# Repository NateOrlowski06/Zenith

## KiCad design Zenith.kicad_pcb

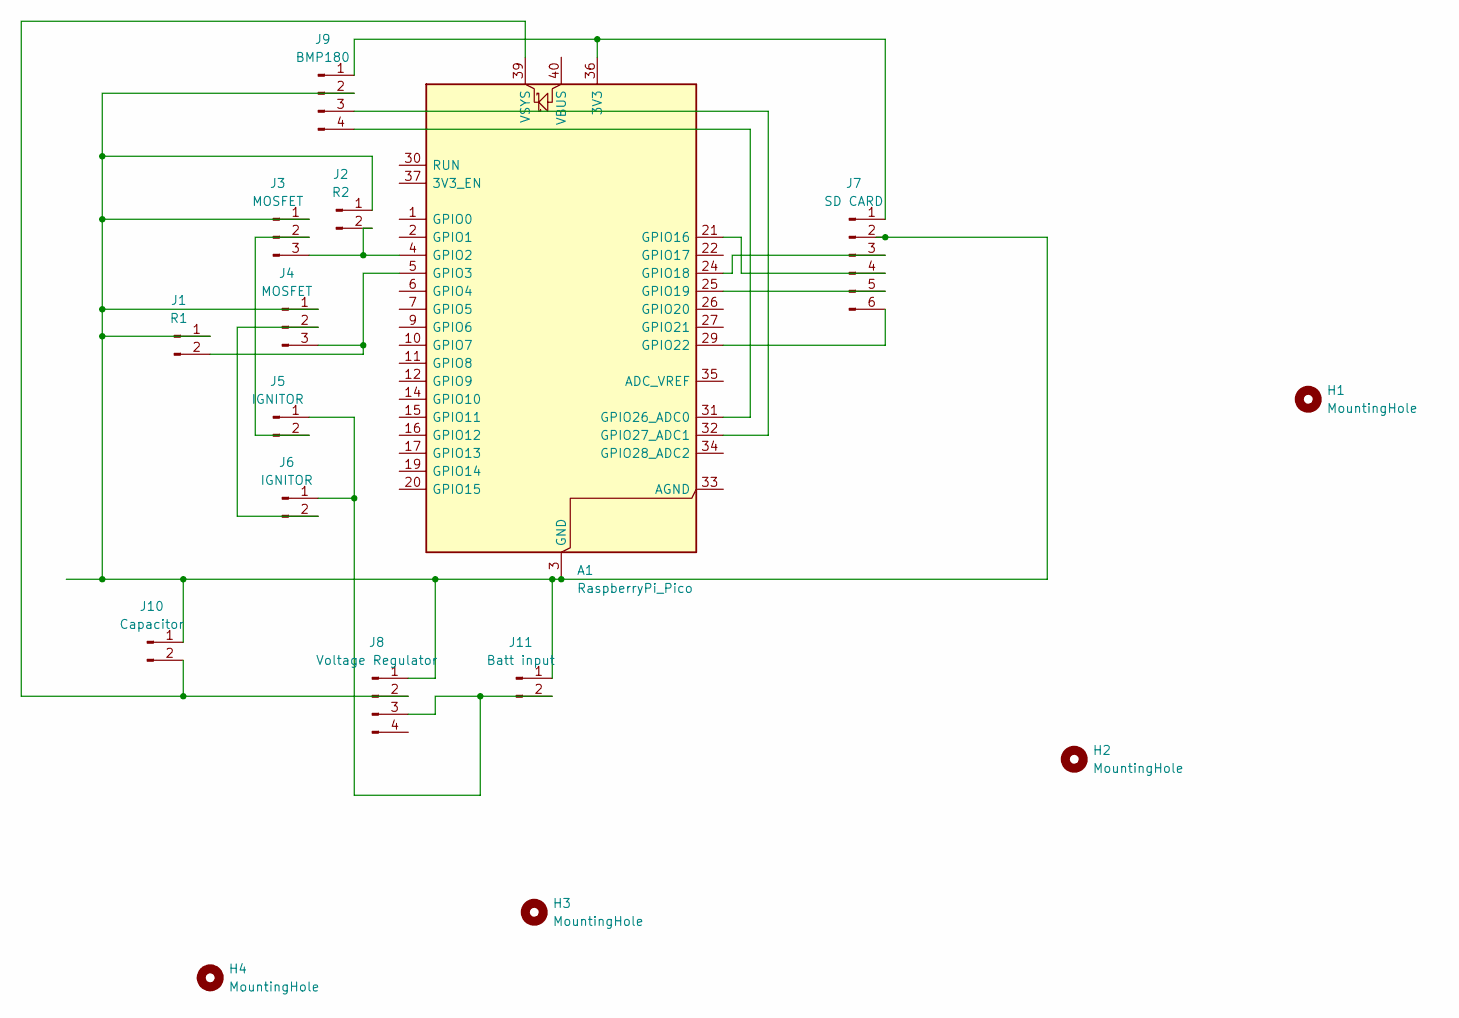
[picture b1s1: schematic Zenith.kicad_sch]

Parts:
A1: RaspberryPi_Pico; RaspberryPi_Pico_Common_Unspecified
H1, H2, H3, H4: MountingHole; MountingHole_2.2mm_M2
J1: R1; PinSocket_1x02_P2.54mm_Vertical
J2: R2; PinSocket_1x02_P2.54mm_Vertical
J3, J4: MOSFET; PinSocket_1x03_P2.54mm_Vertical
J5, J6: IGNITOR; PinSocket_1x02_P2.54mm_Vertical
J7: SD CARD; PinSocket_1x06_P2.54mm_Vertical
J8: Voltage Regulator; PinSocket_1x04_P2.54mm_Vertical
J9: BMP180; PinSocket_1x04_P2.54mm_Vertical
J10: Capacitor; PinSocket_1x02_P2.54mm_Vertical
J11: Batt input; PinSocket_1x02_P2.54mm_Vertical

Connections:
unnamed: A1.36 (3V3), J7.1, J9.1
unnamed: A1.4 (GPIO2), J2.2, J3.3
unnamed: A1.5 (GPIO3), J1.2, J4.3
unnamed: A1.21 (GPIO16), J7.4
unnamed: A1.24 (GPIO18), J7.3
unnamed: A1.25 (GPIO19), J7.5
unnamed: A1.29 (GPIO22), J7.6
unnamed: A1.31 (GPIO26_ADC0), J9.4
unnamed: A1.32 (GPIO27_ADC1), J9.3
unnamed: A1.39 (VSYS), J8.2, J10.2
unnamed: A1.3 (GND), A1.8 (GND), A1.13 (GND), A1.18 (GND), A1.23 (GND), A1.28 (GND), A1.38 (GND), J1.1, J2.1, J3.1, J4.1, J7.2, J8.1, J9.2, J10.1, J11.1
unnamed: J3.2, J5.2
unnamed: J4.2, J6.2
unnamed: J5.1, J6.1, J8.3, J11.2

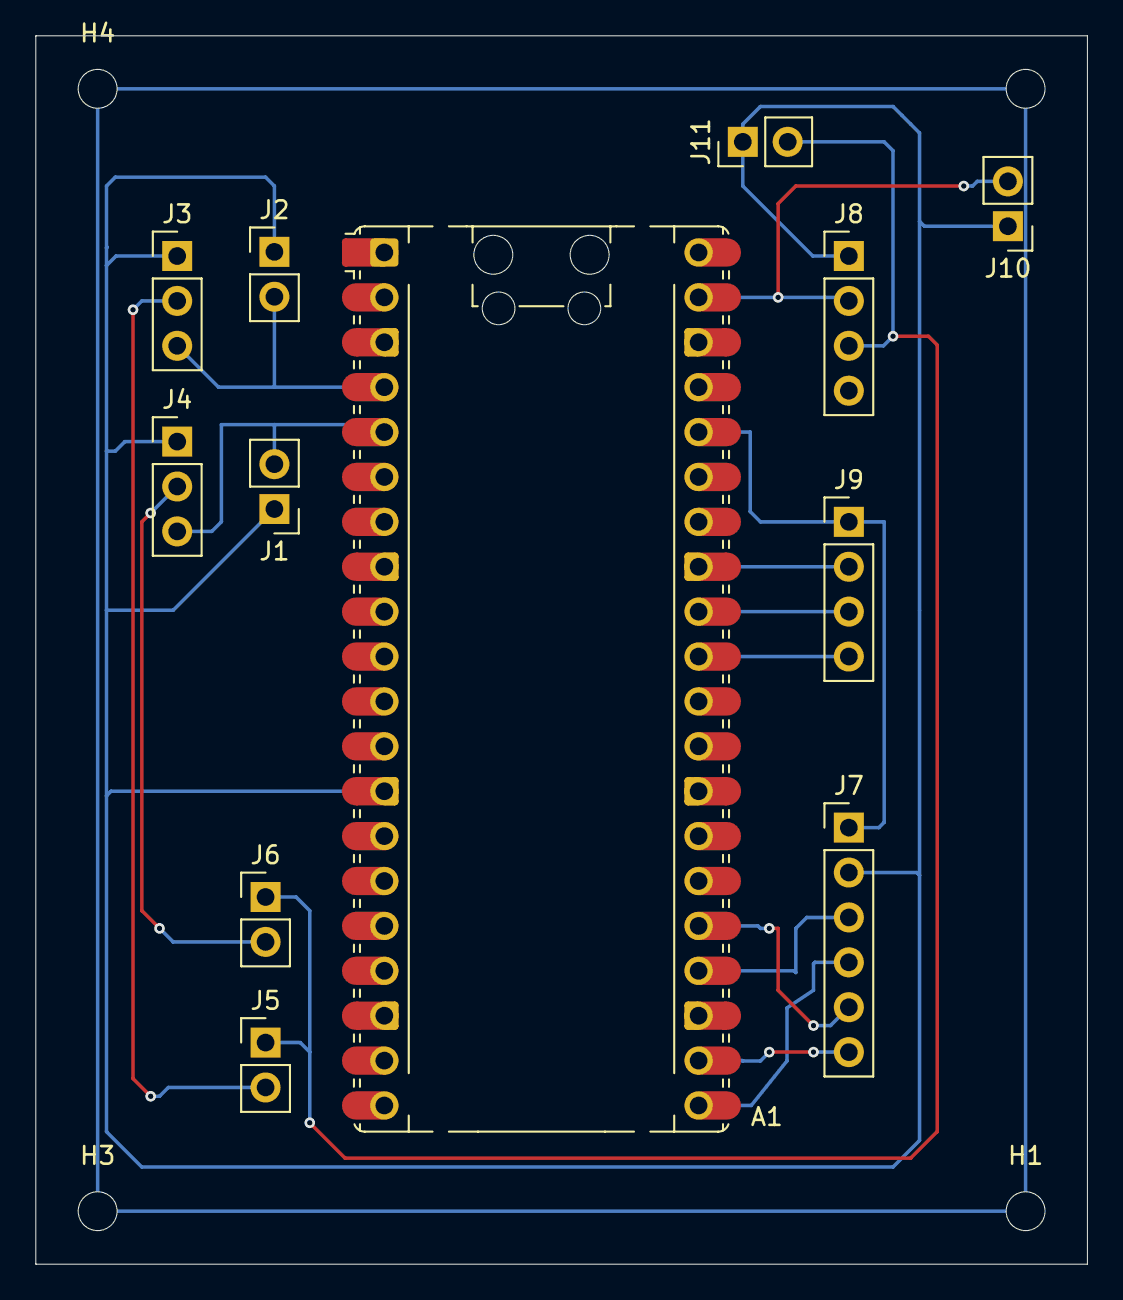
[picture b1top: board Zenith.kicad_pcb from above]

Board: 2 copper layers, 59.5 x 69.5 mm, 16 parts (0 on the bottom side), 14 nets.

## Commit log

2025-05-15 Added BMP180 library
2025-05-15 Added altitude calculation, added scripts to .gitignore
2025-05-15 Pressure Sensor testing
2025-05-16 Changed bmp180 from header only file. Implemented struct data structure for altimeter values. Tested altimeter readings. Wrote some skeleton code for altimeter funcitons.
2025-05-16 Fixed path errors, due to changing file location of bmp180 libraries
2025-05-16 Circular linked list addition
2025-05-16 Impletmented moving average utilizing circular linked list.
2025-05-16 Comments
2025-05-16 Conversion to us instead of ms for more accurate sleep calls
2025-05-16 Slight library optimizations
2025-05-16 Implemented velocity calculations and moving average.
2025-05-16 Fixed initialization of data values
2025-05-16 Differentiated between velocity nodes and altitude nodes
2025-05-16 Correctly implemented change in time between altitude readings.
2025-05-16 Removed LED
2025-05-17 Created state_handler header file with function declarations. Added to cmakelists
2025-05-17 Created state_handler.c and altered header file
2025-05-17 Added height, max height, and max velocity functionality
2025-05-17 Implemented logic for state changes. TODO: determine threshold constants.
2025-05-17 Print statements for serial monitor
2025-05-17 Bug fix: boundary condition where current height == max height resulted in the value of maximum height to be evaluated to zero. Added <= to one of the conditions
2025-05-17 Include guards, variable type changes
2025-05-17 Testing output
2025-05-17 Stoopid velocity error
2025-05-17 Moved all constants to constants.h
2025-05-17 So many stupid errors. actually updated state with the new value each time. Fixed parentheses precedence in handle_coast. fixed logic in handle_boost
2025-05-17 Changed state logic
2025-05-17 Final commit before merge
2025-05-17 Implemented "deployment charges".
2025-05-17 updated state_handler after testing
2025-05-18 Reorganized files between src and header. Also edited CMakeLists file to adjust for this
2025-05-18 A painstaking amount of commenting. And I added functionality for single or dual deploy mode
2025-05-19 Moved inline func to header file
2025-05-19 Branchless logic error resulting in the freefall_start_time to be evaluated to 0 in alternating loop iterations. Fixed.
2025-05-20 Minor changes
2025-05-20 Created bash script for building project
2025-05-21 Corrected state change logic in case that we need to return to standby.
2025-05-21 Included logic for pulsing main deployment charge, made a simple change using += to freefall_start_time
2025-05-21 Micro seconds to seconds conversion error off by factor of 10
2025-05-21 HAHAHA created branch for testing branchless vs branched code
2025-05-21 Logic error
2025-05-21 Updated comments
2025-05-21 Tried to improve code readability
2025-05-21 Integer division error
2025-05-21 Conversion edit
2025-05-21 Added benchmark data
2025-05-21 Removed data
2025-05-21 Added sd card library
2025-05-22 Started to add data logging, implemented multicore processing, created data_packet struct
2025-05-22 Rudimentary test of data logging, code works
2025-05-23 Added data logging on second core
2025-05-23 Working commit
2025-05-23 Data logging works to CSV works, Starts on powerup and ends on landing.
2025-05-24 Data logging starts slightly before takeoff now
2025-05-24 Tidying up, basically ready for launch
2025-05-26 Fixing repo
2025-05-27 Fixing repo part 2
2025-05-28 Added breakout board connector PCB files
2025-05-29 Added kicad parts to models folder
2025-05-29 another commit
2025-05-30 Updated build script and header file for flight
